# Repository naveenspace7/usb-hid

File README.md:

# usb-hid
Experiments for creating a wireless HID device

| Pin#     |      Name     | Functionality |
|----------|:-------------:|--------------:|
| 28 | PB15 | MOSI      |
| 27 |  PB14  |    MISO      |
| 26 | PB13 |  SCK   |
| ? | ? | CSN |
| ? | ? | IRQ |
| ? | ? | CE |

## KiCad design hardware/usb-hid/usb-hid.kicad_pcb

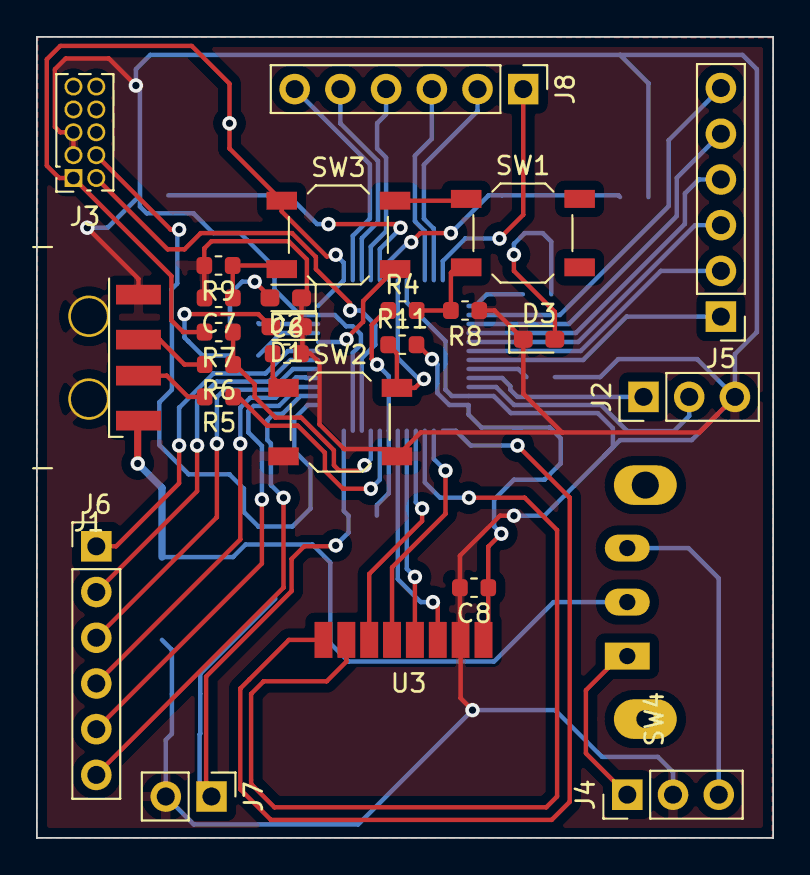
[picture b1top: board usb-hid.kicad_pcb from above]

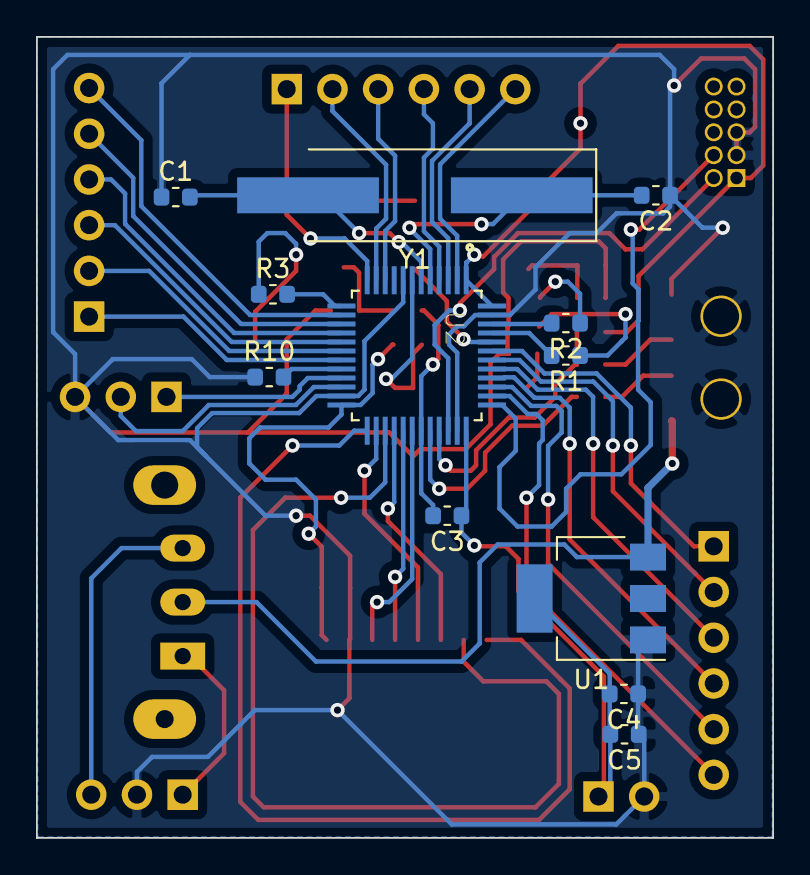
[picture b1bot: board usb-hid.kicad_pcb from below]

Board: 2 copper layers, 40.9 x 44.5 mm, 38 parts (12 on the bottom side), 50 nets.

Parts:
C1, C2, C3, C4, C5, C6, C7, C8: C; C_0603_1608Metric
D1, D2, D3: LED; LED_0603_1608Metric_Pad1.05x0.95mm_HandSolder
J1: PC_USB; USB_A_2.3_2
J2: Debug_UART; PinHeader_1x03_P2.54mm_Vertical
J3: MCU_SWD; PinSocket_2x05_P1.27mm_Vertical
J4: Ext_Power; PinHeader_1x03_P2.54mm_Vertical
J5: Extra-IO-2; PinHeader_1x06_P2.54mm_Vertical
J6: Extra-IO-1; PinHeader_1x06_P2.54mm_Vertical
J7: Conn_01x02_Female; PinHeader_1x02_P2.54mm_Vertical
J8: Extra-IO-0; PinHeader_1x06_P2.54mm_Vertical
R1, R2, R3: 330; R_0603_1608Metric
R4, R5, R6, R8, R10, R11: 22; R_0603_1608Metric
R7: 1.5k; R_0603_1608Metric
R9: 100k; R_0603_1608Metric
SW1: E_SW; SW_SPST_TL3342
SW2: Reset; SW_SPST_TL3342
SW3: Boot; SW_SPST_TL3342
SW4: Power_SW; SW_Aliexpress_3pin
U1: AMS1117-3.3; SOT-223-3_TabPin2
U2: STM32F103C8; QFP50P900X900X160-48N
U3: NRF24L01_SMD; NRF24L01_SMD_PinChange
Y1: Crystal; Crystal_SMD_HC49-SD_HandSoldering

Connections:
/Boot1: C7.1, R9.1, SW3.2, U2.44
/Debug_RX: J2.2, U2.22
/Debug_TX: J2.1, U2.21
/NRST: C6.1, R11.1, SW2.1, U2.7
/SWDCLK_Conn: J3.4, U2.37
/SWDIO_Conn: J3.2, U2.34
/SW_conn: C3.2, R4.1, U2.31
/USB_D+: R6.1, R7.1, U2.33
/USB_D-: R5.1, U2.32
GND: C1.1, C2.1, C4.1, C5.1, C6.2, C7.2, C8.2, D1.1, D2.1, D3.1, J1.4, J1.5, J2.3, J3.3, J3.5, J4.2, J7.2, R8.1, R9.2, R10.1, SW2.2, U1.1, U2.8, U2.23, U2.35, U2.47, U3.2
unnamed: C1.2, U2.6, Y1.2
unnamed: C2.2, U2.5, Y1.1
unnamed: D1.2, R1.1
unnamed: D2.2, R2.1
unnamed: D3.2, R3.1
unnamed: J1.1, SW4.2, U1.3
unnamed: J1.2, R5.2
unnamed: J1.3, R6.2
unnamed: J4.1, SW4.1
unnamed: J4.3, SW4.3
unnamed: J5.1, U2.19
unnamed: J5.2, U2.18
unnamed: J5.3, U2.17
unnamed: J5.4, U2.16
unnamed: J5.5, U2.15
unnamed: J5.6, U2.14
unnamed: J6.1, U2.43
unnamed: J6.2, U2.42
unnamed: J6.3, U2.41
unnamed: J6.4, U2.40
unnamed: J6.5, U2.39
unnamed: J6.6, U2.38
unnamed: J8.1, U2.12
unnamed: J8.2, U2.11
unnamed: J8.3, U2.10
unnamed: J8.4, U2.4
unnamed: J8.5, U2.3
unnamed: J8.6, U2.2
unnamed: R1.2, U2.45
unnamed: R2.2, U2.46
unnamed: R3.2, U2.13
unnamed: R4.2, R8.2, SW1.2
unnamed: R10.2, U2.20
unnamed: U2.25, U3.8
unnamed: U2.26, U3.5
unnamed: U2.27, U3.7
unnamed: U2.28, U3.6
unnamed: U2.29, U3.4
unnamed: U2.30, U3.3
VCC: C3.1, C4.2, C5.2, C8.1, J3.1, J7.1, R7.2, R11.2, SW1.1, SW3.1, U1.2, U2.1, U2.9, U2.24, U2.36, U2.48, U3.1

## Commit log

2020-03-28 Add nrf24 test code - tested with arduino
2020-03-28 Add initial schematic
2020-03-28 Add firmware template
2020-03-28 Add temporary settings files
2020-03-28 Add pins table
2020-03-28 Add connections for NRF24
2020-04-05 Add all the components
2020-04-05 Add more pins
2020-04-05 Position the components
2020-05-17 Add new components and make the sizes proper
2020-05-19 Restruct the schematic for better symbols
2020-07-21 Finish layout
2020-08-08 Add USB in HAL
2020-08-27 Move components
